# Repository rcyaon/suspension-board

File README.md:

# Baja Suspension Load Logger

A data logger that bolts onto one corner of the Baja car and records the forces in the suspension arms while the car drives. The arm design currently uses estimated loads ("3 g bump", "5 g landing"); this board replaces them with measured ones.

| Top | Bottom |
|---|---|
|  |  |

Every connector pin is labeled on the bottom of the board.

For documentation:
- **S/N:** the board's serial number (01, 02, …), to tell identical boards apart.
- **CORNER:** which corner of the car the board is mounted on (LF, RF, LR or RR), so each data file can be matched to its corner.
- **CAL DATE:** the date the strain gauges wired to this board were last calibrated on their arm. The board also checks its own calibration automatically at the start and end of every run; this date is for the arm calibration.

## Does the firmware work?

The real firmware runs on a PC, connected to simulated versions of the board's chips. It is fed a 10 s drive from the Adams model: a bump, whoops, a 0.5 m drop and braking. The SD card file it writes is then checked sample by sample against that input.

**What was logged matches the input.** The blue line is what the firmware saved; the grey line underneath is the Adams input.

**Shock force is right.** Peak landing force logged 4930 N, against 4929 N in the Adams model.

**The firmware adds no error.** The error on each channel is no larger than the noise the simulator itself puts in.

**No samples lost, and the timing is steady.** All 30,616 samples were saved, each within 2 µs of its 512 µs slot.

## What it measures

| Where | What | Sensors |
|---|---|---|
| Lower control arm | Push/pull and bending | 4 strain gauges |
| Upper control arm | Push/pull and fore-aft | 2 strain gauges |
| Toe link | Push/pull | 1 strain gauge |
| Shock | Force, as a cross-check | 1 load cell |
| Shock travel and extras | Position sensors | 4 inputs |
| Chassis motion | Acceleration and rotation | Built-in motion sensor |

All 8 force channels are sampled at the same instant, about 2,000 times a second, onto a microSD card.

## More detail

- [Design specification](spec.md)
- [Schematic (PDF)](fab/rev-b/docs/suspension-load-daq-schematic.pdf)
- [Parts list (CSV)](fab/rev-b/assembly/suspension-load-daq-BOM-full.csv)
- [Ordering files](fab/rev-b/README-fab.md)
- [Firmware build instructions](firmware/README.md)

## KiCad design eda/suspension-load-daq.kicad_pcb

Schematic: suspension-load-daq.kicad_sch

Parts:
C1, C3, C5, C7: 47nF 16V; C_0402_1005Metric
C2, C4, C6, C8, C14, C18, C22, C26, C30, C34, C38, C42, C44, C47, C49, C62, C64, C65, C66, C67, C68, C70, C83: 100nF 16V; C_0402_1005Metric
C11, C12, C15, C16, C19, C20, C23, C24, C27, C28, C31, C32, C35, C36, C39, C40: 1nF 5% 50V C0G; C_0402_1005Metric
C13, C17, C21, C25, C29, C33, C37, C41: 10nF 5% 50V C0G; C_0603_1608Metric
C43, C46, C69, C80, C81: 1uF 16V; C_0402_1005Metric
C45: 220nF 16V; C_0402_1005Metric
C48, C51, C52, C84: 10uF 16V; C_0805_2012Metric
C50: 1uF 25V; C_0603_1608Metric
C53, C63, C71: 4.7uF 16V; C_0603_1608Metric
C58, C59: 12pF 5% 50V C0G; C_0402_1005Metric
C82: EEE-FK1H470P
D1: PESD2CANFD24V
D2: LED RED; LED_0603_1608Metric
D3: LED GREEN; LED_0603_1608Metric
D4: LED BLUE; LED_0603_1608Metric
D5: TPD4E02B04DQAR
D6, D7: 1A 40V Low-IR Schottky; D_SOD-123F
D8: 2A 40V Schottky Rectifier; D_SMA
D9: 18V TVS Diode; D_SMB
D10, D11, D12, D13: 200mA 30V Schottky Rectifier; D_SOD-323
FB1, FB2: 220 100MHz; R_0603_1608Metric
H1, H2, H3, H4: M3 DIN965 TopBottom; MountingHole_3.2mm_M3_DIN965_Pad_TopBottom
J1, J2, J3, J4: B3B-PH-K-S; JST_PH_B3B-PH-K_1x03_P2.00mm_Vertical
J5, J6, J7, J8, J9, J10, J11, J12: B6B-PH-K-S; JST_PH_B6B-PH-K_1x06_P2.00mm_Vertical
J13: 2.54mm 5 x 2 THT Vertical Male; PinHeader_2x05_P2.54mm_Vertical
J14: TC2030-NL_CTX; Tag-Connect_TC2030-IDC-NL_2x03_P1.27mm_Vertical
J15: USB4105
J16: B4B-PH-K-S; JST_PH_B4B-PH-K_1x04_P2.00mm_Vertical
J17: DM3D-SF; microSD_HC_Hirose_DM3D-SF
JP1, JP2, JP3, JP4: SolderJumper-3_P1.3mm_Bridged12_Pad1.0x1.5mm
JP5, JP6, JP7, JP8, JP9, JP10, JP11, JP12, JP13: SolderJumper-2_P1.3mm_Open_Pad1.0x1.5mm
Q1, Q2, Q3, Q4, Q5, Q6, Q7, Q8: PJE138K_R1_00001; SOT-523
R1, R3, R5, R7: 18k 1%; R_0603_1608Metric; not fitted
R2, R4, R6, R8, R74: 10k 1%; R_0603_1608Metric
R9, R15, R21, R27, R33, R39, R45, R51: 100k 0.1%; R_0603_1608Metric
R10, R11, R16, R17, R22, R23, R28, R29, R34, R35, R40, R41, R46, R47, R52, R53: 1k 0.1%; R_0603_1608Metric
R12, R13, R14, R18, R19, R20, R24, R25, R26, R30, R31, R32, R36, R37, R38, R42, R43, R44, R48, R49, R50, R54, R55, R56: 350 0.1%; R_0805_2012Metric; not fitted
R57, R76, R79, R96: 100k; R_0402_1005Metric
R58: 1 1%; R_0603_1608Metric
R59: 24.9k 0.1%; R_0603_1608Metric
R63, R64, R77: 10k; R_0402_1005Metric
R73: 100k 1%; R_0603_1608Metric
R75: 33; R_0402_1005Metric
R78: 100k; R_0402_1005Metric; not fitted
R80: 10k; R_0402_1005Metric; not fitted
R81: 120 1%; R_0805_2012Metric
R82, R83: 5.1k 1%; R_0402_1005Metric
R84, R85: 1k; R_0402_1005Metric
R86: 2.2k; R_0402_1005Metric
R87, R88: 10k 0.1%; R_0603_1608Metric; not fitted
R89, R90: 4.7k; R_0402_1005Metric
R91, R92, R93, R94, R95: 47k; R_0402_1005Metric
R97: 10k 1%; R_0402_1005Metric
R98: 15k 1%; R_0402_1005Metric
SW1: KMR211NGLFS; KMR2x1NGLFS
TP1, TP2, TP3, TP4, TP5, TP6, TP7: TestPoint_Small; TestPoint_Pad_D1.5mm
U2: LT3042xMSE; MSOP-10-1EP_3x3mm_P0.5mm_EP1.68x1.88mm
U3: STM32F412CEU6; ST_UFQFPN-48-1EP_7x7mm_P0.5mm_EP5.6x5.6mm
U6: LP5907MFX-3.3; SOT-23-5
U7: ADS131M08xPBS; TQFP-32_5x5mm_P0.5mm
Y1: 8MHz 10pF; Crystal_SMD_3225-4Pin_3.2x2.5mm

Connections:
/ADC_CLKIN: R75.2, R76.1, TP1.1, U7.23 (XTAL1/CLKIN)
/ADC_DRDY: TP2.1, U3.3 (PC14-OSC32_IN), U7.18 (~DRDY)
/ADC_MCLK: R75.1, U3.29 (PA8)
/ADC_REFIN: C47.1, R87.2, R88.1, U7.14 (REFIN)
/ADC_SPI_CLK: J17.5 (CLK), R79.1, U3.15 (PA5), U7.19 (SCLK)
/ADC_SPI_CS: R77.1, U3.38 (PA15), U7.17 (~CS)
/ADC_SPI_MISO: J17.7 (DAT0), R92.1, U3.16 (PA6), U7.20 (DOUT)
/ADC_SPI_MOSI: J17.3 (CMD), R78.1, R91.1, U3.17 (PA7), U7.21 (DIN)
/ADC_SYNC_RST: R64.1, R80.1, U3.20 (PB2), U7.16 (~SYNC/~RESET)
/AIN0N: C11.1, C13.2, R10.2, U7.30 (AIN0N)
/AIN0P: C12.1, C13.1, R11.2, U7.29 (AIN0P)
/AIN1N: C15.1, C17.2, R16.2, U7.31 (AIN1N)
/AIN1P: C16.1, C17.1, R17.2, U7.32 (AIN1P)
/AIN2N: C19.1, C21.2, R22.2, U7.2 (AIN2N)
/AIN2P: C20.1, C21.1, R23.2, U7.1 (AIN2P)
/AIN3N: C23.1, C25.2, R28.2, U7.3 (AIN3N)
/AIN3P: C24.1, C25.1, R29.2, U7.4 (AIN3P)
/AIN4N: C27.1, C29.2, R34.2, U7.6 (AIN4N)
/AIN4P: C28.1, C29.1, R35.2, U7.5 (AIN4P)
/AIN5N: C31.1, C33.2, R40.2, U7.7 (AIN5N)
/AIN5P: C32.1, C33.1, R41.2, U7.8 (AIN5P)
/AIN6N: C35.1, C37.2, R46.2, U7.10 (AIN6N)
/AIN6P: C36.1, C37.1, R47.2, U7.9 (AIN6P)
/AIN7N: C39.1, C41.2, R52.2, U7.11 (AIN7N)
/AIN7P: C40.1, C41.1, R53.2, U7.12 (AIN7P)
/AUX1: C1.1, D10.2 (A), R1.1, R2.2, U3.10 (PA0)
/AUX1_SIG: J1.2, R2.1
/AUX1_V_SENSOR: C2.1, J1.1, JP1.2
/AUX2: C3.1, D11.2 (A), R3.1, R4.2, U3.11 (PA1)
/AUX2_SIG: J2.2, R4.1
/AUX2_V_SENSOR: C4.1, J2.1, JP2.2
/AUX3: C5.1, D12.2 (A), R5.1, R6.2, U3.14 (PA4)
/AUX3_SIG: J3.2, R6.1
/AUX3_V_SENSOR: C6.1, J3.1, JP3.2
/AUX4: C7.1, D13.2 (A), R7.1, R8.2, U3.18 (PB0)
/AUX4_SIG: J4.2, R8.1
/AUX4_V_SENSOR: C8.1, J4.1, JP4.2
/CAN_TERM: JP13.1, R81.2
/CH0_CAL: Q1.3 (D), R9.2
/CH0_HALF_MID: JP5.2, R12.2, R13.1
/CH0_IN_N: J5.3, JP5.1, R10.1
/CH0_IN_P: J5.2, R9.1, R11.1
/CH0_QTR: J5.5, R14.1
/CH1_CAL: Q2.3 (D), R15.2
/CH1_HALF_MID: JP6.2, R18.2, R19.1
/CH1_IN_N: J6.3, JP6.1, R16.1
/CH1_IN_P: J6.2, R15.1, R17.1
/CH1_QTR: J6.5, R20.1
/CH2_CAL: Q3.3 (D), R21.2
/CH2_HALF_MID: JP7.2, R24.2, R25.1
/CH2_IN_N: J7.3, JP7.1, R22.1
/CH2_IN_P: J7.2, R21.1, R23.1
/CH2_QTR: J7.5, R26.1
/CH3_CAL: Q4.3 (D), R27.2
/CH3_HALF_MID: JP8.2, R30.2, R31.1
/CH3_IN_N: J8.3, JP8.1, R28.1
/CH3_IN_P: J8.2, R27.1, R29.1
/CH3_QTR: J8.5, R32.1
/CH4_CAL: Q5.3 (D), R33.2
/CH4_HALF_MID: JP9.2, R36.2, R37.1
/CH4_IN_N: J9.3, JP9.1, R34.1
/CH4_IN_P: J9.2, R33.1, R35.1
/CH4_QTR: J9.5, R38.1
/CH5_CAL: Q6.3 (D), R39.2
/CH5_HALF_MID: JP10.2, R42.2, R43.1
/CH5_IN_N: J10.3, JP10.1, R40.1
/CH5_IN_P: J10.2, R39.1, R41.1
/CH5_QTR: J10.5, R44.1
/CH6_CAL: Q7.3 (D), R45.2
/CH6_HALF_MID: JP11.2, R48.2, R49.1
/CH6_IN_N: J11.3, JP11.1, R46.1
/CH6_IN_P: J11.2, R45.1, R47.1
/CH6_QTR: J11.5, R50.1
/CH7_CAL: Q8.3 (D), R51.2
/CH7_HALF_MID: JP12.2, R54.2, R55.1
/CH7_IN_N: J12.3, JP12.1, R52.1
/CH7_IN_P: J12.2, R51.1, R53.1
/CH7_QTR: J12.5, R56.1
/EXC_EN: R57.1, U2.3 (EN/UV), U3.40 (PB4)
/EXC_SET: C53.1, R59.1, U2.7 (SET)
/I2C_SCL: J13.7, R89.1, U3.42 (PB6)
/I2C_SDA: J13.8, R90.1, U3.43 (PB7)
/LED_ERR: R84.1, U3.41 (PB5)
/LED_ERR_A: D2.2 (A), R84.2
/LED_LOG: R85.1, U3.21 (PB10)
/LED_LOG_A: D3.2 (A), R85.2
/LED_PWR_A: D4.2 (A), R86.2
/MCU_BOOT0: R63.1, SW1.1, SW1.4 (1), U3.44 (BOOT0)
/MCU_HSE_IN: C58.1, U3.5 (PH0-OSC_IN), Y1.1
/MCU_HSE_OUT: C59.1, U3.6 (PH1-OSC_OUT), Y1.3
/NRST: C62.1, J14.3 (~RESET), U3.7 (NRST)
/SD_CS: J17.2 (DAT3/CD), R95.1, U3.31 (PA10)
/SD_DAT1: J17.8 (DAT1), R93.1
/SD_DAT2: J17.1 (DAT2), R94.1
/SD_DET: J17.10 (DET_A), U3.2 (PC13)
/SHUNT_CAL: Q1.1 (G), Q2.1 (G), Q3.1 (G), Q4.1 (G), Q5.1 (G), Q6.1 (G), Q7.1 (G), Q8.1 (G), R96.1, U3.39 (PB3)
/SWD_SWCLK: J14.4 (SWCLK/TCK), U3.37 (PA14)
/SWD_SWDIO: J14.2 (SWDIO/TMS), U3.34 (PA13)
/UART_RX: J13.6, U3.13 (PA3)
/UART_TX: J13.5, U3.12 (PA2)
/USB_CC1: D5.4 (IO3), D5.7 (IO3), J15.A5 (CC1), R82.1
/USB_CC2: D5.5 (IO4), D5.6 (IO4), J15.B5 (CC2), R83.1
/USB_D_N: D5.2 (IO2), D5.9 (IO2), J15.A7 (D-), J15.B7 (D-), U3.32 (PA11)
/USB_D_P: D5.1 (IO1), D5.10 (IO1), J15.A6 (D+), J15.B6 (D+), U3.33 (PA12)
/VBAT_MON: C83.1, R73.2, R74.1, U3.19 (PB1)
/VBUS_SENSE: R97.2, R98.1, U3.30 (PA9)
ADC_CAP: C45.1, U7.24 (CAP)
CANH: D1.1 (K1), J16.3, R81.1; also elsewhere on the board
CANL: D1.2 (K2), J16.4, JP13.2; also elsewhere on the board
CAN_RX: U3.45 (PB8); also elsewhere on the board
CAN_TX: U3.46 (PB9); also elsewhere on the board
CE92F33B_B5EE_566D_91AA_04935ED1A8A1.U2.NC_LT3042xMSE_PG: U2.4 (PG)
CE419F7E_AAEF_5640_A00C_559494572CE8.U7.NC_ADS131M08xPBS_XTAL2: U7.22 (XTAL2)
E5DDBF15_4968_5B0E_9312_A38794FA11BE.J13.NC_2_54mm_5_x_2_THT_Vertical_Male_Pin_9: J13.9
E5DDBF15_4968_5B0E_9312_A38794FA11BE.J13.NC_2_54mm_5_x_2_THT_Vertical_Male_Pin_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: J13.10
EXC: C14.1, C18.1, C22.1, C26.1, C30.1, C34.1, C38.1, C42.1, C52.1, J5.1, J6.1, J7.1, J8.1, J9.1, J10.1, J11.1, J12.1, R12.1, R18.1, R24.1, R30.1, R36.1, R42.1, R48.1, R54.1, R87.1, TP3.1, U2.9 (OUTS), U2.10 (OUT)
EXC_VIN_FILT: C51.1, R58.2, U2.1 (IN), U2.2 (IN), U2.6 (PGFB)
GND: C1.2, C2.2, C3.2, C4.2, C5.2, C6.2, C7.2, C8.2, C11.2, C12.2, C14.2, C15.2, C16.2, C18.2, C19.2, C20.2, C22.2, C23.2, C24.2, C26.2, C27.2, C28.2, C30.2, C31.2, C32.2, C34.2, C35.2, C36.2, C38.2, C39.2, C40.2, C42.2, C43.2, C44.2, C45.2, C46.2, C47.2, C48.2, C49.2, C50.2, C51.2, C52.2, C53.2, C58.2, C59.2, C62.2, C63.2, C64.2, C65.2, C66.2, C67.2, C68.2, C69.2, C70.2, C71.2, C80.2, C81.2, C82.2 (-), C83.2, C84.2, D1.3 (CC), D2.1 (K), D3.1 (K), D4.1 (K), D5.3 (GND), D5.8 (GND), D9.1 (A1), H1.1, H2.1, H3.1, H4.1, J1.3, J2.3, J3.3, J4.3, J5.4, J5.6, J6.4, J6.6, J7.4, J7.6, J8.4, J8.6, J9.4, J9.6, J10.4, J10.6, J11.4, J11.6, J12.4, J12.6, J13.3, J13.4, J14.5 (GND), J15.A1 (GND), J15.A12 (GND), J15.B1 (GND), J15.B12 (GND), J15.SH (SHIELD), J16.2, J17.6 (VSS), J17.9 (DET_B), J17.11 (SHIELD), Q1.2 (S), Q2.2 (S), Q3.2 (S), Q4.2 (S), Q5.2 (S), Q6.2 (S), Q7.2 (S), Q8.2 (S), R1.2, R3.2, R5.2, R7.2, R13.2, R14.2, R19.2, R20.2, R25.2, R26.2, R31.2, R32.2, R37.2, R38.2, R43.2, R44.2, R49.2, R50.2, R55.2, R56.2, R57.2, R59.2, R63.2, R64.2, R74.2, R76.2, R78.2, R79.2, R82.2, R83.2, R88.2, R96.2, R98.2, TP4.1, U2.5 (ILIM), U2.8 (GND), U2.11 (GND), U3.8 (VSSA/VREF-), U3.23 (VSS), U3.35 (VSS), U3.47 (VSS), U3.49 (EP), U6.2 (GND), U7.13 (AGND), U7.25 (DGND), U7.27 (AGND), U7.28 (AGND), Y1.2 (G), Y1.4 (G); also elsewhere on the board
IMU_INT1: U3.4 (PC15-OSC32_OUT); also elsewhere on the board
IMU_SPI_CLK: U3.26 (PB13); also elsewhere on the board
IMU_SPI_CS: U3.25 (PB12); also elsewhere on the board
IMU_SPI_MISO: U3.27 (PB14); also elsewhere on the board
IMU_SPI_MOSI: U3.28 (PB15); also elsewhere on the board
MCU_VCAP: C63.1, U3.22 (VCAP_1)
PWR_V5_ANA: C80.1, FB2.2, U6.1 (IN), U6.3 (EN)
PWR_VPROT: C82.1 (+), D8.1 (K), R73.1; also elsewhere on the board
SHEET_1E38873B_1565_589A_9F67_7DA908C7A1CF./USB_SBU1: J15.A8 (SBU1)
SHEET_1E38873B_1565_589A_9F67_7DA908C7A1CF./USB_SBU2: J15.B8 (SBU2)
SHEET_2FA17A4D_9B43_582C_8717_1449C502FD6B.U6.NC_LP5907MFX-3_3_NC: U6.4 (NC)
SHEET_86AE2C84_4DAF_53FF_BA88_4A842EC6F995.J14.NC_TC2030-NL_CTX_SWO/TDO: J14.6 (SWO/TDO)
V3V3: C46.1, C48.1, C49.1, C64.1, C65.1, C66.1, C67.1, C68.1, C71.1, D10.1 (K), D11.1 (K), D12.1 (K), D13.1 (K), FB1.1, J13.1, J14.1 (VTref), J17.4 (VDD), R77.2, R80.2, R86.1, R89.2, R90.2, R91.2, R92.2, R93.2, R94.2, R95.2, SW1.2, SW1.3 (2), TP5.1, U3.1 (VBAT), U3.24 (VDD), U3.36 (VDD), U3.48 (VDD), U7.26 (DVDD); also elsewhere on the board
V3V3A: C43.1, C44.1, C81.1, TP6.1, U6.5 (OUT), U7.15 (AVDD)
VBUS: C50.1, D7.2 (A), J15.A4 (VBUS), J15.A9 (VBUS), J15.B4 (VBUS), J15.B9 (VBUS), R97.1
VDDA: C69.1, C70.1, FB1.2, JP1.1, JP2.1, JP3.1, JP4.1, U3.9 (VDDA/VREF+)
VIN_VEH: D8.2 (A), D9.2 (A2), J16.1

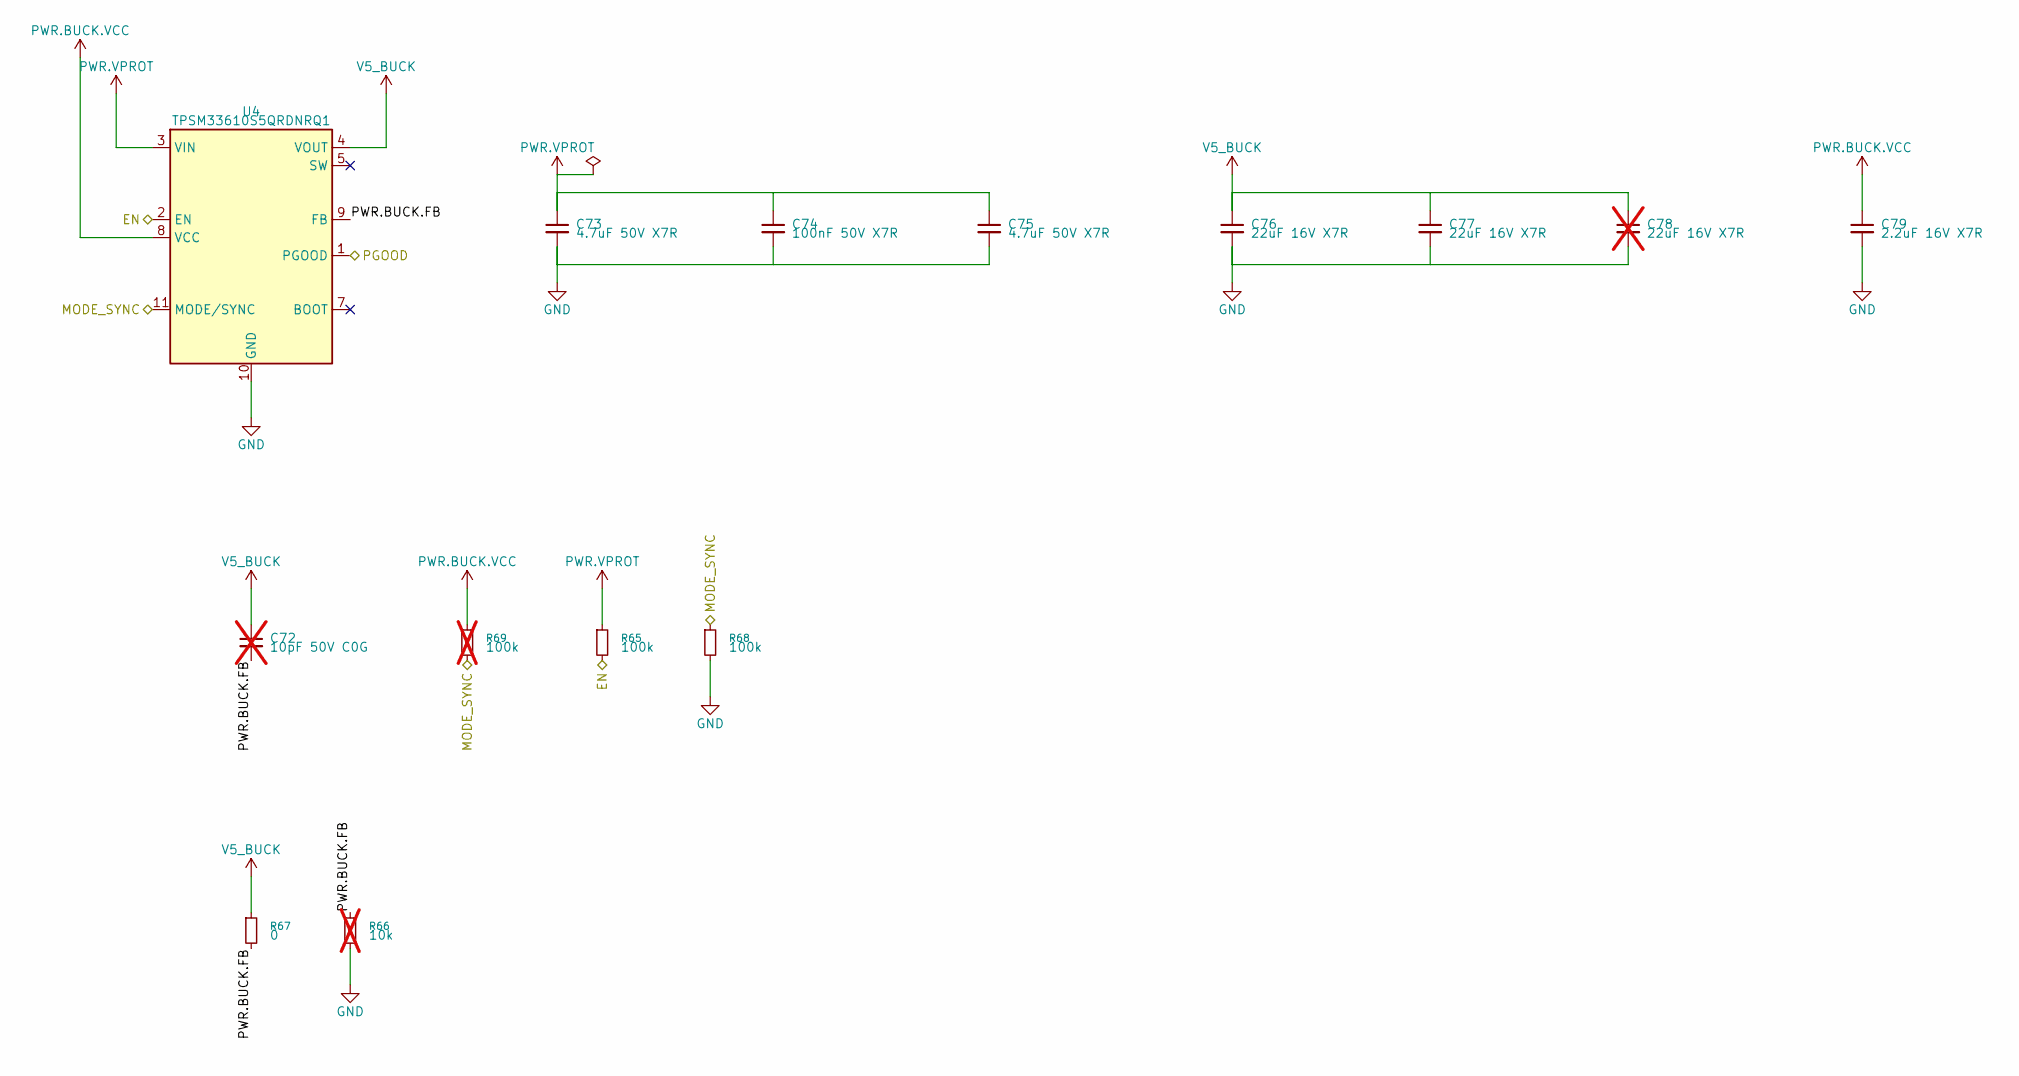
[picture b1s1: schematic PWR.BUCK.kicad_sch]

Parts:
C72: 10pF 50V C0G; C_0402_1005Metric; not fitted
C73, C75: 4.7uF 50V X7R; C_1210_3225Metric
C74: 100nF 50V X7R; C_0402_1005Metric
C76, C77: 22uF 16V X7R; C_1210_3225Metric
C78: 22uF 16V X7R; C_1210_3225Metric; not fitted
C79: 2.2uF 16V X7R; C_0603_1608Metric
R65, R68: 100k; R_0402_1005Metric
R66: 10k; R_0402_1005Metric; not fitted
R67: 0; R_0402_1005Metric
R69: 100k; R_0402_1005Metric; not fitted
U4: TPSM33610S5QRDNRQ1; TPSM336xx-Q1

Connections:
/BUCK/PWR_BUCK_FB: C72.2, R66.1, R67.2, U4.9 (FB)
/PWR_BUCK_EN: R65.2, U4.2 (EN)
/PWR_BUCK_MODE_SYNC: R68.1, R69.2, U4.11 (MODE/SYNC)
GND: C73.2, C74.2, C75.2, C76.2, C77.2, C78.2, C79.2, R66.2, R68.2, U4.10 (GND); also elsewhere on the board
PWR_BUCK_VCC: C79.1, R69.1, U4.8 (VCC)
PWR_VPROT: C73.1, C74.1, C75.1, R65.1, U4.3 (VIN); also elsewhere on the board
SHEET_76AEE5BD_A69C_56AF_AE87_0C38A51049F7./PWR_BUCK_PGOOD: U4.1 (PGOOD)
SHEET_76AEE5BD_A69C_56AF_AE87_0C38A51049F7.U4.NC_TPSM33610S5QRDNRQ1_BOOT: U4.7 (BOOT)

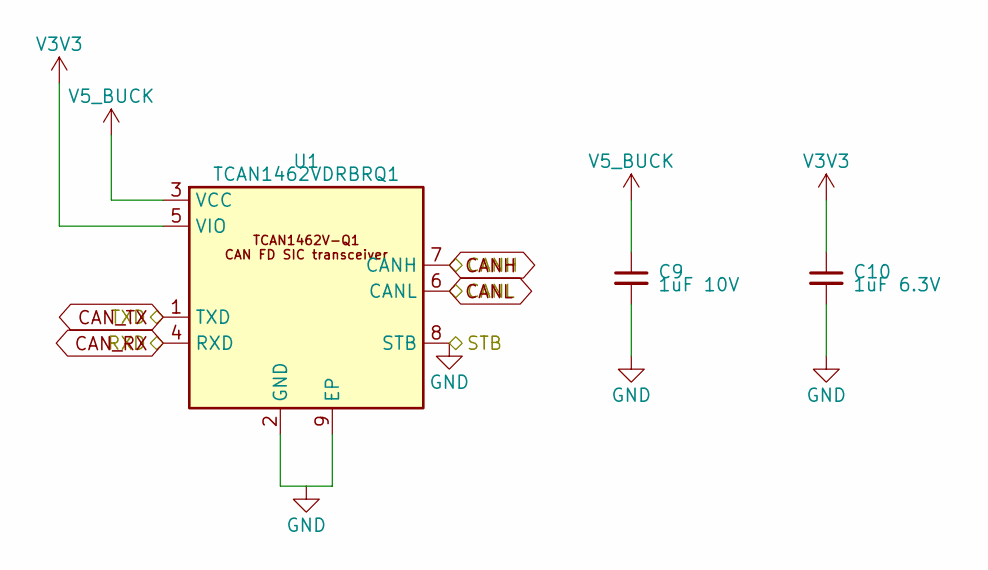
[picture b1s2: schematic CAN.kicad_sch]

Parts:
C9: 1uF 10V; C_0402_1005Metric
C10: 1uF 6.3V; C_0402_1005Metric
U1: TCAN1462VDRBRQ1; TCAN1462V-Q1-DRB

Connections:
CANH: U1.7 (CANH); also elsewhere on the board
CANL: U1.6 (CANL); also elsewhere on the board
CAN_RX: U1.4 (RXD); also elsewhere on the board
CAN_TX: U1.1 (TXD); also elsewhere on the board
GND: C9.2, C10.2, U1.2 (GND), U1.8 (STB), U1.9 (EP); also elsewhere on the board
V3V3: C10.1, U1.5 (VIO); also elsewhere on the board

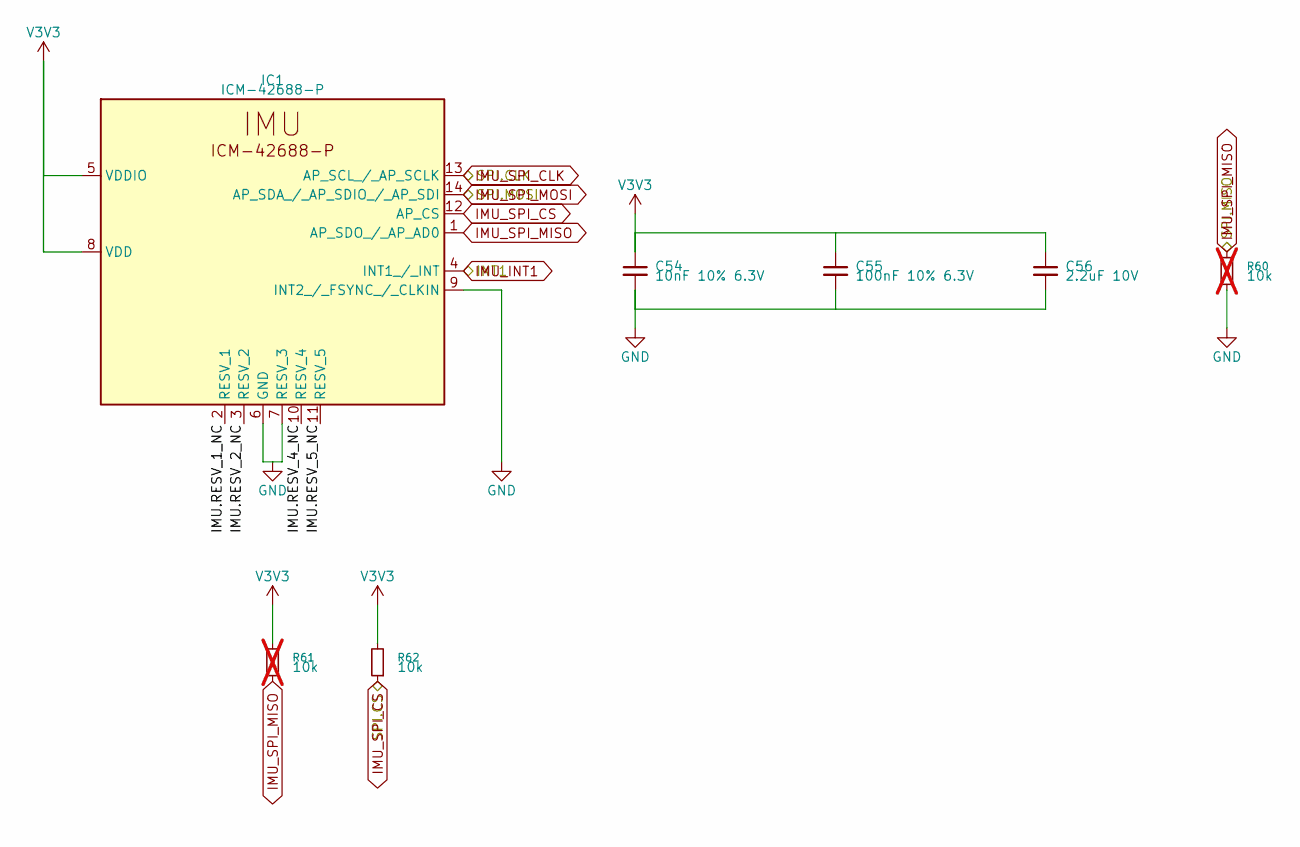
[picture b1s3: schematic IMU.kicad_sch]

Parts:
C54: 10nF 10% 6.3V; C_0402_1005Metric
C55: 100nF 10% 6.3V; C_0402_1005Metric
C56: 2.2uF 10V; C_0603_1608Metric
IC1: ICM-42688-P; IIM42352
R60, R61: 10k; R_0402_1005Metric; not fitted
R62: 10k; R_0402_1005Metric

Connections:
GND: C54.2, C55.2, C56.2, IC1.6 (GND), IC1.7 (RESV_3), IC1.9 (INT2_/_FSYNC_/_CLKIN), R60.2; also elsewhere on the board
IMU_INT1: IC1.4 (INT1_/_INT); also elsewhere on the board
IMU_SPI_CLK: IC1.13 (AP_SCL_/_AP_SCLK); also elsewhere on the board
IMU_SPI_CS: IC1.12 (AP_CS), R62.1; also elsewhere on the board
IMU_SPI_MISO: IC1.1 (AP_SDO_/_AP_AD0), R60.1, R61.1; also elsewhere on the board
IMU_SPI_MOSI: IC1.14 (AP_SDA_/_AP_SDIO_/_AP_SDI); also elsewhere on the board
SHEET_8522DDAD_AE9A_56B5_B069_4220863B1849./IMU/IMU_RESV_1_NC: IC1.2 (RESV_1)
SHEET_8522DDAD_AE9A_56B5_B069_4220863B1849./IMU/IMU_RESV_2_NC: IC1.3 (RESV_2)
SHEET_8522DDAD_AE9A_56B5_B069_4220863B1849./IMU/IMU_RESV_4_NC: IC1.10 (RESV_4)
SHEET_8522DDAD_AE9A_56B5_B069_4220863B1849./IMU/IMU_RESV_5_NC: IC1.11 (RESV_5)
V3V3: C54.1, C55.1, C56.1, IC1.5 (VDDIO), IC1.8 (VDD), R61.2, R62.2; also elsewhere on the board

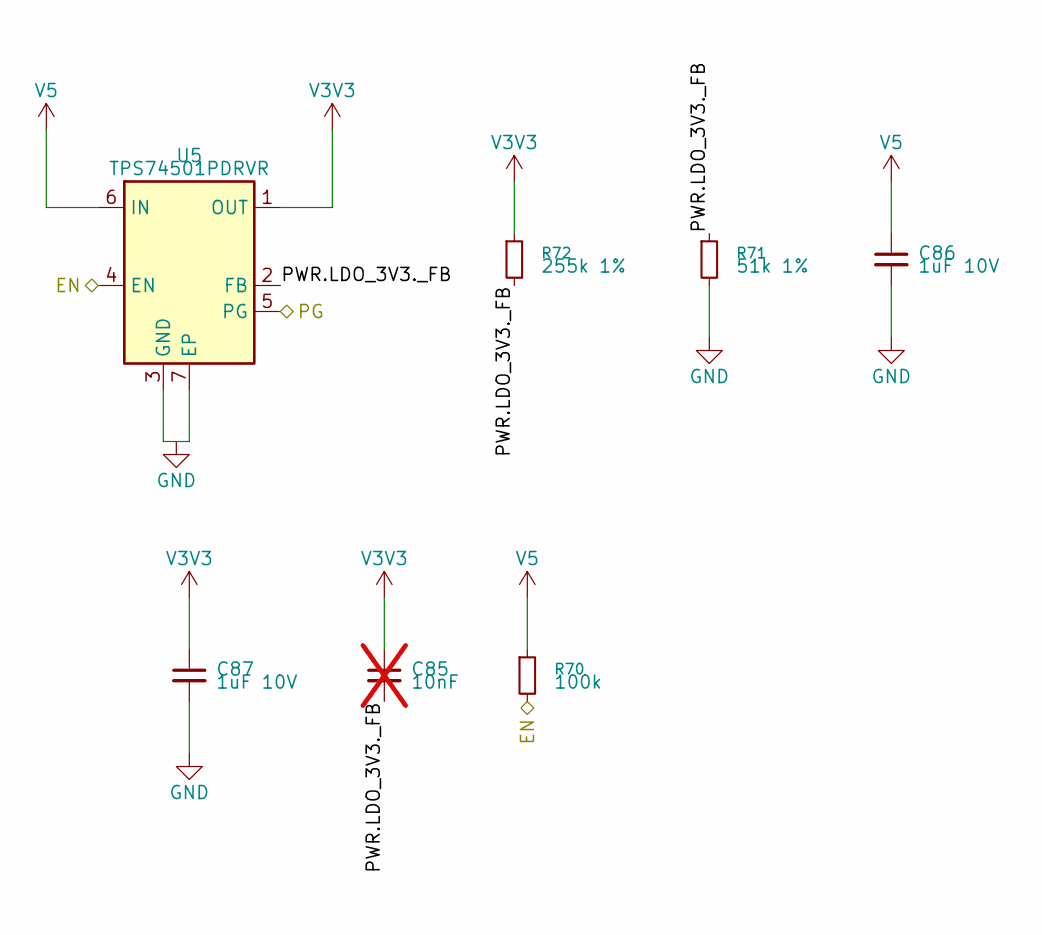
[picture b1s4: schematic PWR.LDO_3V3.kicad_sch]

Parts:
C85: 10nF; C_0402_1005Metric; not fitted
C86, C87: 1uF 10V; C_0402_1005Metric
R70: 100k; R_0402_1005Metric
R71: 51k 1%; R_0402_1005Metric
R72: 255k 1%; R_0402_1005Metric
U5: TPS74501PDRVR; TPS74x01P

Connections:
/LDO_3V3/PWR_LDO_3V3_FB: C85.2, R71.1, R72.2, U5.2 (FB)
/PWR_LDO_3V3_EN: R70.2, U5.4 (EN)
GND: C86.2, C87.2, R71.2, U5.3 (GND), U5.7 (EP); also elsewhere on the board
SHEET_28B8B799_7A7C_55D0_9ACD_16A5C6B80815./PWR_LDO_3V3_PG: U5.5 (PG)
V3V3: C85.1, C87.1, R72.1, U5.1 (OUT); also elsewhere on the board

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
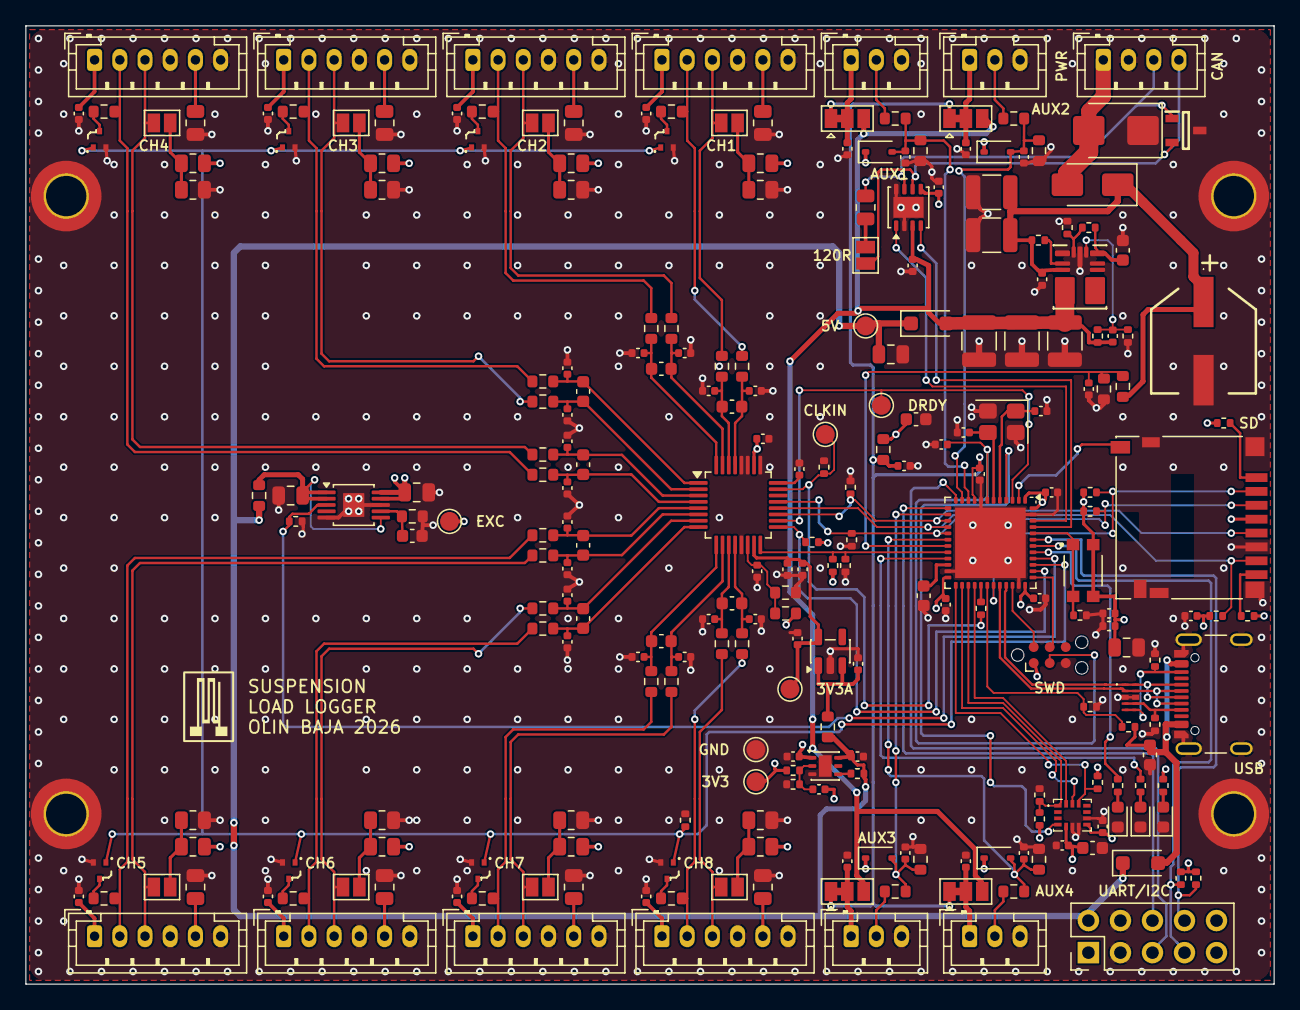
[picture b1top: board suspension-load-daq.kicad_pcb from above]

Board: 4 copper layers, 99.0 x 76.0 mm, 256 parts (0 on the bottom side), 135 nets.

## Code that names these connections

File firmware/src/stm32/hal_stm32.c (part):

/* hal.h for the STM32F412CEU6 board (pin map: docs/mcu-migration.md).
 * Clocks: HSE 8 MHz -> PLL 96 MHz SYSCLK, 48 MHz USB clock, APB1 48 MHz,
 * APB2 96 MHz. MCO1 outputs HSE/1 on PA8 as the ADS131M08 clock. */
#include "../hal.h"
#include "regs.h"

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
/* ---- GPIO ---- */
void gpio_adc_reset(int a) { put(GPIOB, 2, !a); }
void gpio_exc_en(int on) { put(GPIOB, 4, on); }
void gpio_shunt(int on) { put(GPIOB, 3, on); }
void led_log(int on) { put(GPIOB, 10, on); }
void led_err(int on) { put(GPIOB, 5, on); }
int gpio_sd_present(void) { return !(GPIO_IDR(GPIOC) & (1u << 13)); }   /* switch to GND when inserted */
int gpio_vbus(void) { return (GPIO_IDR(GPIOA) >> 9) & 1; }
void adc_cs(int s) { put(GPIOA, 15, !s); }
void sd_cs(int s) { put(GPIOA, 10, !s); }
void imu_cs(int s) { put(GPIOB, 12, !s); }

static void gpio_init(void) {
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    /* outputs first to safe levels: CS high, excitation/shunt off, ADC in reset */
    put(GPIOA, 10, 1); put(GPIOA, 15, 1); put(GPIOB, 12, 1);
    put(GPIOB, 2, 0); put(GPIOB, 3, 0); put(GPIOB, 4, 0); put(GPIOB, 5, 0); put(GPIOB, 10, 0);
    pin(GPIOA, 10, OUT, 0, 0); pin(GPIOA, 15, OUT, 0, 0);          /* SD_CS, ADC_CS (PA15 leaves JTDI) */
    pin(GPIOB, 2, OUT, 0, 0); pin(GPIOB, 3, OUT, 0, 0);            /* ADC_SYNC_RST, SHUNT_CAL (PB3 leaves JTDO) */
    pin(GPIOB, 4, OUT, 0, 0); pin(GPIOB, 5, OUT, 0, 0);            /* EXC_EN (PB4 leaves NJTRST), LED_ERR */
    pin(GPIOB, 10, OUT, 0, 0); pin(GPIOB, 12, OUT, 0, 0);          /* LED_LOG, IMU_CS */
    pin(GPIOA, 0, AN, 0, 0); pin(GPIOA, 1, AN, 0, 0); pin(GPIOA, 4, AN, 0, 0);
    pin(GPIOB, 0, AN, 0, 0); pin(GPIOB, 1, AN, 0, 0);
    pin(GPIOA, 2, AF, 7, 0); pin(GPIOA, 3, AF, 7, 1);              /* USART2 */
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    pin(GPIOB, 13, AF, 5, 0); pin(GPIOB, 14, AF, 5, 0); pin(GPIOB, 15, AF, 5, 0); /* SPI2 */
    pin(GPIOB, 8, AF, 8, 1); pin(GPIOB, 9, AF, 8, 0);              /* CAN1 RX/TX */
    pin(GPIOA, 8, AF, 0, 0);                                       /* MCO1 -> ADC CLKIN */
    pin(GPIOA, 9, IN, 0, 0);                                       /* VBUS_SENSE */
    pin(GPIOC, 13, IN, 0, 1);                                      /* SD_DET, pull-up */
    pin(GPIOC, 14, IN, 0, 0); pin(GPIOC, 15, IN, 0, 0);            /* ADC_DRDY, IMU_INT1 */
}

/* ---- SPI ---- */
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}
static void exti_init(void) {
    RCC_APB2ENR |= 1u << 14;
    SYSCFG_EXTICR(3) = (SYSCFG_EXTICR(3) & ~(0xFu << 8)) | (2u << 8);   /* EXTI14 = PC14 */
    EXTI_FTSR |= 1u << 14;
    NVIC_IPR8(IRQ_EXTI15_10) = 0x00;                                    /* highest */
    NVIC_ISER(IRQ_EXTI15_10 / 32) = 1u << (IRQ_EXTI15_10 % 32);
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
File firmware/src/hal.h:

/* Hardware abstraction. Everything above this line is plain C that also runs
 * in the PC simulator (test/sim). hal_stm32.c implements it for the board. */
#ifndef HAL_H
#define HAL_H
#include <stdint.h>

/* time: free-running 1 MHz counter from the same 8 MHz crystal as the ADC */
uint32_t hal_now_us(void);
void hal_delay_us(uint32_t us);

/* interrupts */
uint32_t hal_irq_save(void);
void hal_irq_restore(uint32_t s);
void hal_drdy_irq_enable(int en);   /* ADS131M08 DRDY falling edge on PC14 */

/* SPI1: shared by ADC (mode 1) and microSD (mode 0) */
enum { SPI1_ADC, SPI1_SD_SLOW, SPI1_SD_FAST };
void spi1_config(int mode);
uint8_t spi1_xfer(uint8_t b);
void spi1_write(const uint8_t *buf, uint32_t n);   /* transmit only */
void spi1_xfer_buf(const uint8_t *tx, uint8_t *rx, uint32_t n);
void adc_cs(int selected);
void sd_cs(int selected);

/* SPI2: IMU only */
void spi2_xfer_buf(const uint8_t *tx, uint8_t *rx, uint32_t n);
void imu_cs(int selected);

/* GPIO */
void gpio_adc_reset(int asserted);  /* PB2, active low on the pin */
void gpio_exc_en(int on);           /* PB4 */
void gpio_shunt(int on);            /* PB3, all 8 shunt FETs */
void led_log(int on);               /* PB10 */
void led_err(int on);               /* PB5 */
int gpio_sd_present(void);          /* PC13 */
int gpio_vbus(void);                /* PA9 */

/* MCU ADC1: AUX1-4 + battery, one scan per bridge frame */
#define AUX_N 5
void aux_trigger(void);
void aux_read(uint16_t out[AUX_N]);

/* CAN (bxCAN1, 500 kbit/s classic). can_init returns 0 if the bus/transceiver
 * is not available (USB-only power). Received frames arrive via app_can_rx. */
int can_init(void);
int can_send(uint16_t id, const uint8_t *data, uint8_t len);

/* UART2 console */
void uart_putc(char c);
int uart_getc(void);                /* -1 when empty */

uint32_t hal_uid(int word);         /* 96-bit unique ID, word 0..2 */

/* callbacks into the application (called from interrupt context) */
void app_drdy_isr(void);
void app_can_rx(uint16_t id, const uint8_t *data, uint8_t len, uint32_t t_us);

#endif

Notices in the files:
parts and their libraries:
License: Apache-2.0
